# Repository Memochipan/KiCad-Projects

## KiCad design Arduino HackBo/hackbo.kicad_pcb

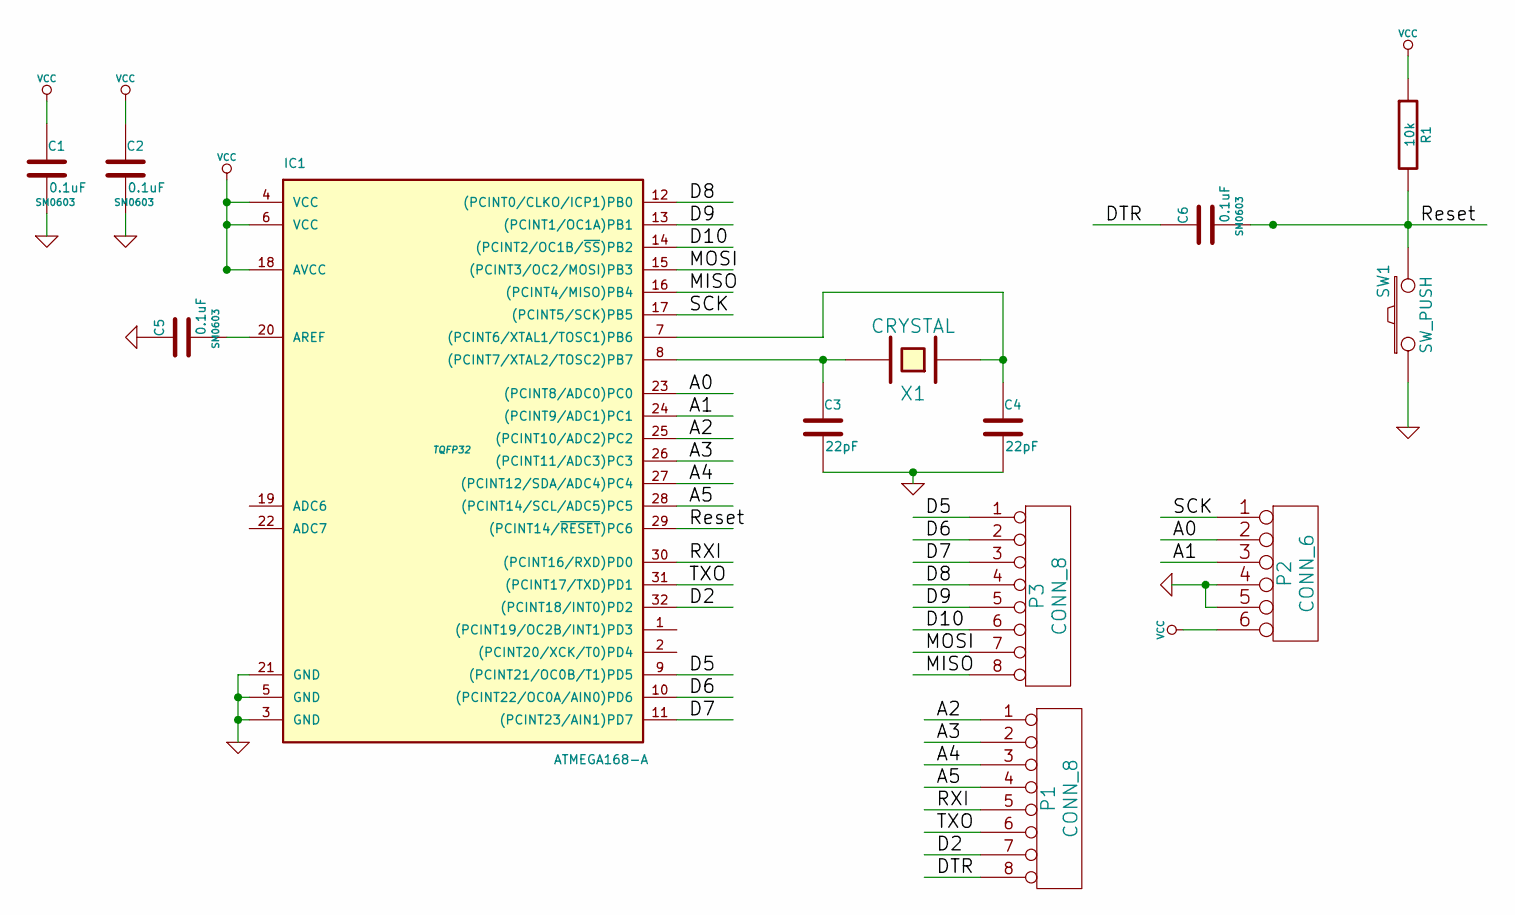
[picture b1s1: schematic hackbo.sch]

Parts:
C1, C2, C5, C6: 0.1uF; SM0603
C3, C4: 22pF; SM0603
IC1: ATMEGA168-A; TQFP32
P1, P3: CONN_8; SIL-8
P2: CONN_6; SIL-6
R1: 10k; SM0603
SW1: SW_PUSH; SW_PUSH_SMALL
X1: CRYSTAL; HC-49V

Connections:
/A0: IC1.23 ((PCINT8/ADC0)PC0), P2.2
/A1: IC1.24 ((PCINT9/ADC1)PC1), P2.3
/A2: IC1.25 ((PCINT10/ADC2)PC2), P1.1
/A3: IC1.26 ((PCINT11/ADC3)PC3), P1.2
/A4: IC1.27 ((PCINT12/SDA/ADC4)PC4), P1.3
/A5: IC1.28 ((PCINT14/SCL/ADC5)PC5), P1.4
/D2: IC1.32 ((PCINT18/INT0)PD2), P1.7
/D5: IC1.9 ((PCINT21/OC0B/T1)PD5), P3.1
/D6: IC1.10 ((PCINT22/OC0A/AIN0)PD6), P3.2
/D7: IC1.11 ((PCINT23/AIN1)PD7), P3.3
/D8: IC1.12 ((PCINT0/CLKO/ICP1)PB0), P3.4
/D9: IC1.13 ((PCINT1/OC1A)PB1), P3.5
/D10: IC1.14 ((PCINT2/OC1B/~SS~)PB2), P3.6
/DTR: C6.1, P1.8
/MISO: IC1.16 ((PCINT4/MISO)PB4), P3.8
/MOSI: IC1.15 ((PCINT3/OC2/MOSI)PB3), P3.7
/RXI: IC1.30 ((PCINT16/RXD)PD0), P1.5
/Reset: C6.2, IC1.29 ((PCINT14/~RESET~)PC6), R1.2, SW1.2
/SCK: IC1.17 ((PCINT5/SCK)PB5), P2.1
/TXO: IC1.31 ((PCINT17/TXD)PD1), P1.6
GND: C1.2, C2.2, C3.2, C4.2, C5.1, IC1.3 (GND), IC1.5 (GND), IC1.21 (GND), P2.4, P2.5, SW1.1
unnamed: C5.2, IC1.20 (AREF)
unnamed: C4.1, IC1.7 ((PCINT6/XTAL1/TOSC1)PB6), X1.1
unnamed: C3.1, IC1.8 ((PCINT7/XTAL2/TOSC2)PB7), X1.2
VCC: C1.1, C2.1, IC1.4 (VCC), IC1.6 (VCC), IC1.18 (AVCC), P2.6, R1.1

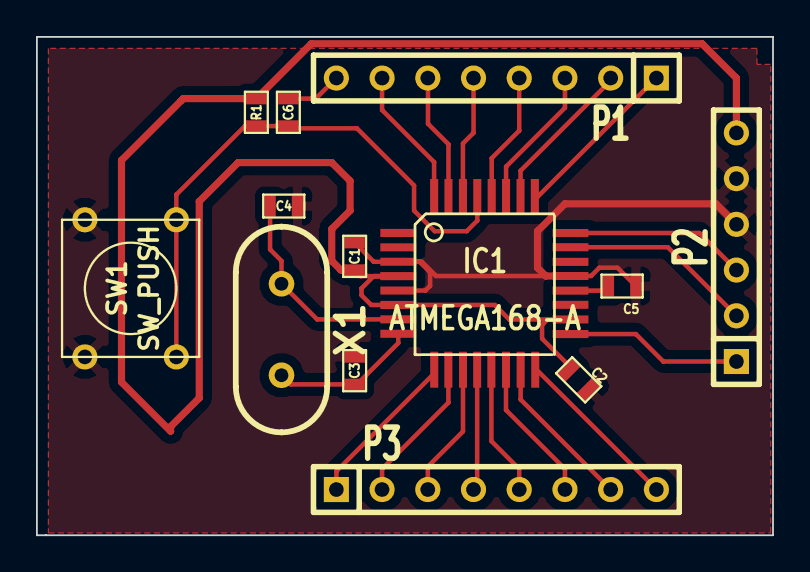
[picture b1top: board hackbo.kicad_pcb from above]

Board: 2 copper layers, 40.9 x 27.7 mm, 13 parts (0 on the bottom side), 25 nets.

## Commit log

2014-08-20 :lollipop: Added .gitattributes & .gitignore files
2014-08-20 Versión Preliminar Arduino (HackBo 2014-08-13)
    Usando KiCad Build (2013-07-07 BZR 4022)-stable en Windows 8 (32 bits).
2014-08-20 Adicionado pantallazo de la versión de 2014-08-13.
2014-08-27 Adicionado Reset y Alimentación (HackBo 2014-08-26)
    - Se adicionó el circuito de reset y las conexiones para la
    alimentación.
    - Se eliminaron componentes no utilizados.
    - Se generaron los archivos GERBER.
